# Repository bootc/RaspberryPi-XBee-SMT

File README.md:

Raspberry Pi XBee ZB SMT Backpack
=================================

This project is for a Raspberry Pi expansion board to accommodate a Digi XBee
ZB SMT board.

The main intention of targeting the ZB SMT is so that the module can be driven
over the SPI bus instead of using the UART. This has several advantages, one of
which is it does not use up the UART so that it can still be used for other
functionality.

The expansion board / backpack is able to host a non-SMT module using the
standard 2mm header. Note that it is impossible to use SPI for modules
connected using this header as the pins are not connected.

Solder jumpers are available to select which SPI chipselect line to use, to
connect the ZB UART to the Raspberry Pi's UART and to connect GPIOs to various
ZB pins (DTR/SLEEP_RQ and INTR).

Submodules
----------

This git repo uses git submodules to pull in SparkFun's Eagle libraries. If you
clone this repo, please run the following commands to pull in the libraries:

```
git submodule init
git submodule update
```

Licensing
---------

<br />This work is licensed under a <a rel="license" href="http://creativecommons.org/licenses/by-sa/2.0/uk/">Creative Commons Attribution-ShareAlike 2.0 UK: England &amp; Wales License</a>.

&copy;2012 Chris Boot.

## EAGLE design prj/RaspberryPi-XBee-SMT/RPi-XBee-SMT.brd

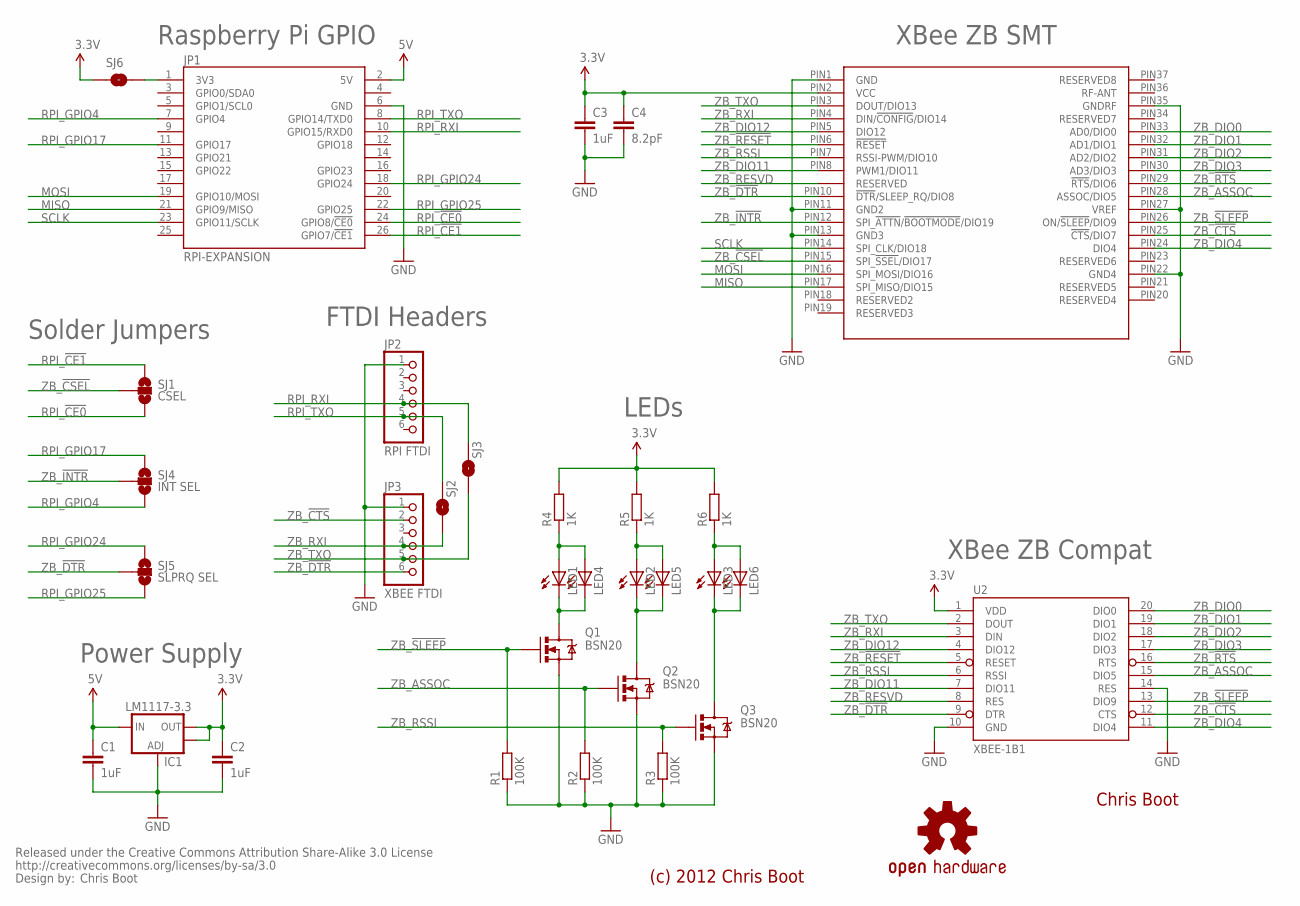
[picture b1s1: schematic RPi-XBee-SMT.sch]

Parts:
C1, C2, C3: 1uF; C0805
C4: 8.2pF; C0805
IC1: LM1117-3.3; SOT223
JP1: RPI-EXPANSION; 2X13
JP2: RPI FTDI; 1X06
JP3: XBEE FTDI; 1X06
LED1, LED2, LED3: LED-3MM-NO_SILK; LED3MM-NS
LED4, LED5, LED6: LED0603; LED-0603
Q1, Q2, Q3: BSN20; SOT23-3
R1, R2, R3: 100K; R0805
R4, R5, R6: 1K; R0805
SJ1: CSEL; SJ_3
SJ2, SJ3, SJ6: SOLDERJUMPERNO; SJ_2S-NO
SJ4: INT SEL; SJ_3
SJ5: SLPRQ SEL; SJ_3
U1: QUBIQ_XBEE-SMT; QUBIQ_FLAT-RF
U2: XBEE-1B1; XBEE-1
U$3: CREATIVE_COMMONS
U$4: OSHW-LOGOL; OSHW-LOGO-L

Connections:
3.3V: C2.1, C3.1, C4.1, IC1.2 (OUT), IC1.4 (OUT), R4.2, R5.2, R6.2, SJ6.1, U1.PIN2 (VCC), U2.1 (VDD)
5V: C1.1, IC1.3 (IN), JP1.2 (5V)
GND: C1.2, C2.2, C3.2, C4.2, IC1.1 (ADJ), JP1.6 (GND), JP2.1, JP3.1, Q1.2 (S), Q2.2 (S), Q3.2 (S), R1.1, R2.1, R3.1, U1.PIN1 (GND), U1.PIN11 (GND2), U1.PIN13 (GND3), U1.PIN22 (GND4), U1.PIN27 (VREF), U1.PIN35 (GNDRF), U2.10 (GND), U2.14 (RES)
MISO: JP1.21 (GPIO9/MISO), U1.PIN17 (SPI_MISO/DIO15)
MOSI: JP1.19 (GPIO10/MOSI), U1.PIN16 (SPI_MOSI/DIO16)
unnamed: LED1.K (C), LED4.C, Q1.3 (D)
unnamed: LED2.K (C), LED5.C, Q2.3 (D)
unnamed: LED3.K (C), LED6.C, Q3.3 (D)
unnamed: LED1.A, LED4.A, R4.1
unnamed: LED2.A, LED5.A, R5.1
unnamed: LED3.A, LED6.A, R6.1
RPI_3.3V: JP1.1 (3V3), SJ6.2
RPI_!CE0: JP1.24 (GPIO8/!CE0), SJ1.3
RPI_!CE1: JP1.26 (GPIO7/!CE1), SJ1.1
RPI_GPIO4: JP1.7 (GPIO4), SJ4.3
RPI_GPIO17: JP1.11 (GPIO17), SJ4.1
RPI_GPIO24: JP1.18 (GPIO24), SJ5.1
RPI_GPIO25: JP1.22 (GPIO25), SJ5.3
RPI_RXI: JP1.10 (GPIO15/RXD0), JP2.4, SJ3.2
RPI_TXO: JP1.8 (GPIO14/TXD0), JP2.5, SJ2.2
SCLK: JP1.23 (GPIO11/SCLK), U1.PIN14 (SPI_CLK/DIO18)
ZB_!CSEL: SJ1.2, U1.PIN15 (SPI_!SSEL!/DIO17)
ZB_!CTS: JP3.2, U1.PIN25 (!CTS!/DIO7), U2.12 (CTS)
ZB_!DTR: JP3.6, SJ5.2, U1.PIN10 (!DTR!/SLEEP_RQ/DIO8), U2.9 (DTR)
ZB_!INTR: SJ4.2, U1.PIN12 (SPI_!ATTN!/!BOOTMODE!/DIO19)
ZB_!RESET: U1.PIN6 (!RESET), U2.5 (RESET)
ZB_!RTS: U1.PIN29 (!RTS!/DIO6), U2.16 (RTS)
ZB_!SLEEP: Q1.1 (G), R1.2, U1.PIN26 (ON/!SLEEP!/DIO9), U2.13 (DIO9)
ZB_ASSOC: Q2.1 (G), R2.2, U1.PIN28 (ASSOC/DIO5), U2.15 (DIO5)
ZB_DIO0: U1.PIN33 (AD0/DIO0), U2.20 (DIO0)
ZB_DIO1: U1.PIN32 (AD1/DIO1), U2.19 (DIO1)
ZB_DIO2: U1.PIN31 (AD2/DIO2), U2.18 (DIO2)
ZB_DIO3: U1.PIN30 (AD3/DIO3), U2.17 (DIO3)
ZB_DIO4: U1.PIN24 (DIO4), U2.11 (DIO4)
ZB_DIO11: U1.PIN8 (PWM1/DIO11), U2.7 (DIO11)
ZB_DIO12: U1.PIN5 (DIO12), U2.4 (DIO12)
ZB_RESVD: U1.PIN9 (RESERVED), U2.8 (RES)
ZB_RSSI: Q3.1 (G), R3.2, U1.PIN7 (RSSI-PWM/DIO10), U2.6 (RSSI)
ZB_RXI: JP3.4, SJ2.1, U1.PIN4 (DIN/!CONFIG!/DIO14), U2.3 (DIN)
ZB_TXO: JP3.5, SJ3.1, U1.PIN3 (DOUT/DIO13), U2.2 (DOUT)

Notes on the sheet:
Chris Boot
(c) 2012 Chris Boot
XBee ZB SMT
XBee ZB Compat
Raspberry Pi GPIO
LEDs
Power Supply
Solder Jumpers
FTDI Headers

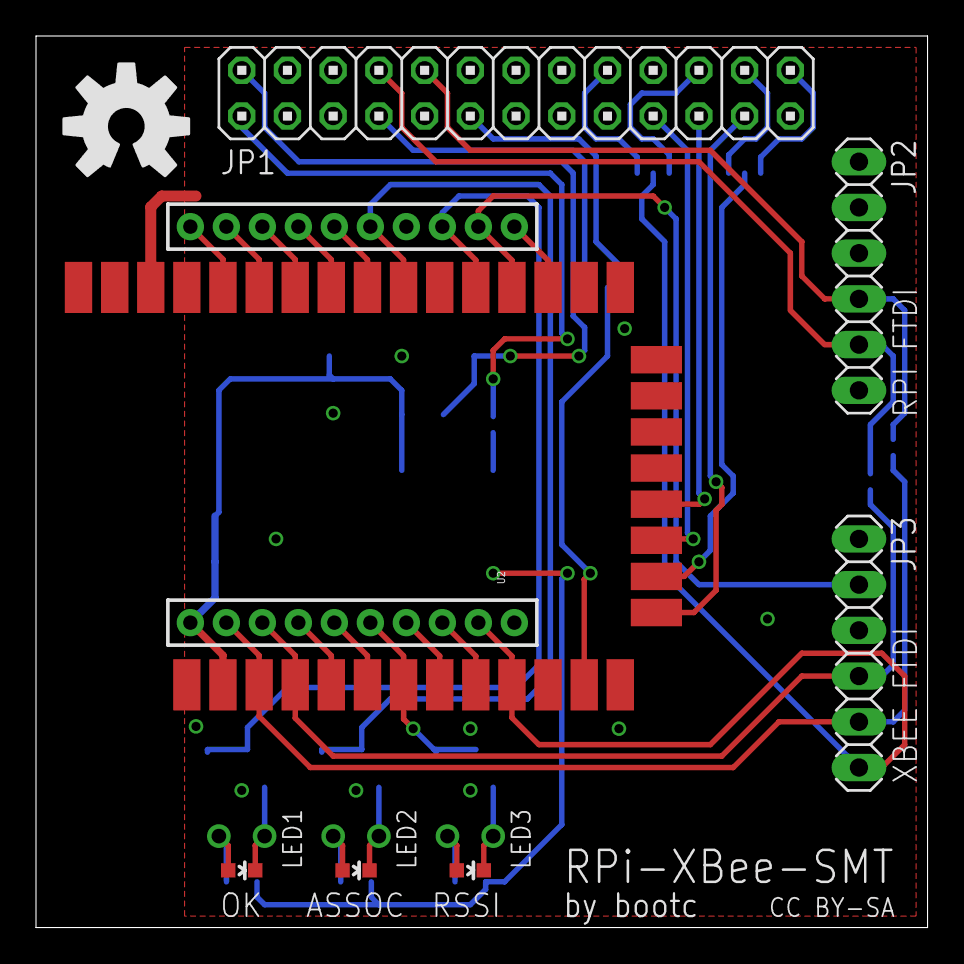
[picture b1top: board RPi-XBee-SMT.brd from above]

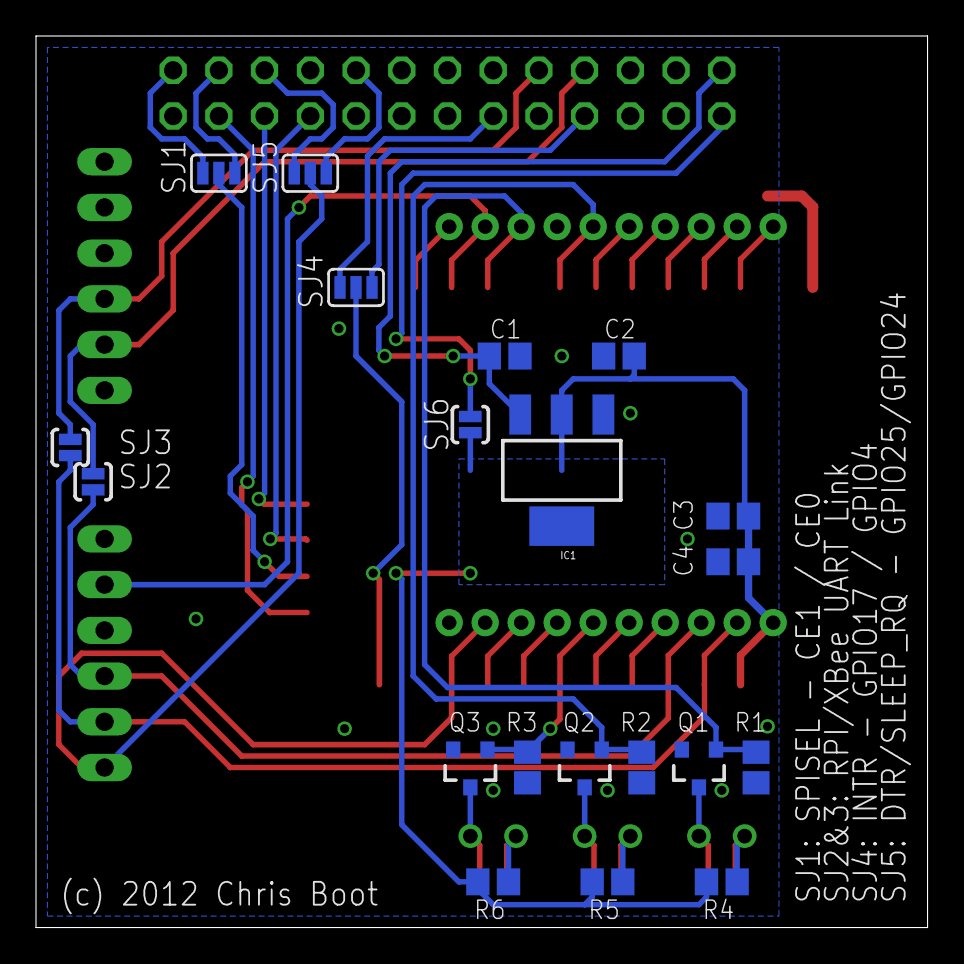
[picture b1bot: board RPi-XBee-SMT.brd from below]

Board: 2 copper layers, 49.5 x 49.5 mm, 33 parts (20 on the bottom side), 40 nets.

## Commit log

2012-06-19 First public release.
2012-06-19 Add .gitignore file.
2012-06-19 Move JP1 label back onto the board.
2012-06-20 Add solder jumper to power XBee from RPI 3.3V
    This will allow people to omit the LDO if they would rather power the
    XBee module straight from the Raspberry Pi's 3.3V rail.
    This update also does some minor trace re-routing and moves some text
    around the board a bit.
2012-06-20 Rename proj => prj
2012-06-20 Move SparkFun libraries around a bit.
2012-06-20 Oops, last commit broke the submodule.
2012-06-29 Move the Eagle files into a project directory.
2012-06-29 Fix up some 10mil traces to 12mil

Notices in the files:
prj/RaspberryPi-XBee-SMT/RPi-XBee-SMT.brd:
CC BY-SA
parts and their libraries:
SparkFun-PowerIC: Licensing: CC v3.0 Share-Alike You are welcome to use this library for commercial purposes.
SparkFun-Aesthetics: Released under the Creative Commons Attribution Share-Alike 3.0 License
SparkFun-Aesthetics: http://creativecommons.org/licenses/by-sa/3.0
